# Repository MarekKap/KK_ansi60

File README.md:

# KK_ansi60
60% mechanical keyboard

KK_ansi60 keyboard is inspired by [GH60 open source keyboard](https://github.com/komar007/gh60).
Case and mounting plate are made from one piece of aluminium alloy. This feature allows very
solid and compact design. On the other hand only ane switch layout is supported.
Keyboard support TMK firmware, so everything is open source and customizable. On default there
are two base layers. Active layer is indicated with LED under FN1 or FN2 key.

## Build instructions
1. Solder all SMDs parts on PCB.
2. Temporary solder USB cable on connector `J1`.
3. Load firmware.
   1. Plug USB cable into computer.
   2. Run command `dmesg`, you should see `Product: ATm32U4DFU` in output list. If not,
      double check your soldering and check if you have ATMEGA32u4 with DFU bootloader.
   3. Clone repo `git clone "https://github.com/MarekKap/KK_ansi60"`.
   4. Go to firmware directory `cd KK_ansi60/Firmware/`.
   5. Compile program `make`.
   6. Load firmware into keyboard `sudo make dfu`.
   7. Unplug USB cable from computer.
4. Desolder USB cable.
5. Install keycaps stabilizers on top plate.
6. Install some switchies on on top plate. Start with edges and long keys.
7. Flip the top plate and put PCB on installed switches.
8. Cut switch legs. Keep in mind, there is only 2mm space between PCB and bottom plate.
9. Solder switches on PCB.
10. Install, cut and solder rest of the switches.
11. Install, cut and solder `LED1` and `LED2`.
12. Remove insulation from USB cable. Use heat shring tube or your nylon cable sleeve will
    start stripping over time.
13. Use cable tie to hold USB cable in place.
14. Solder free USB wires to connector `J1`. Keep `D+` and `D-` wires twisted as long as
    possible.
15. Hold down USB wires using kapton tape on PCB.
16. Install CNC legs with screws on bottom plate and put self adhesive pads in place.
17. Stick a insulation sticker on bottom plate (PCB side).
18. Screw bootom and top piece together with M2.5 screws.
19. Plug USB cable into computer and enjoy your keyboard. :-)

## Where to buy
| Item                        | Seller                       | Price [EUR] | Note                |
| --------------------------- | ---------------------------- | ----------- | ------------------- |
| Resistor 22R (R1, R2)       | [Farnell][1]                 |        0.09 | for 10 pcs          |
| Resistor 10K (R3, R4)       | [Farnell][2]                 |        0.09 | for 10 pcs          |
| Resistor 82R (R5, R6)       | [Farnell][3]                 |        0.13 | for 10 pcs          |
| Capacitor 10uF (C1)         | [Farnell][4]                 |        0.80 | for 5 pcs           |
| Capacitor 0.1uF (C2-C6, C8) | [Farnell][5]                 |        0.52 | for 10 pcs          |
| Capacitor 1uF (C7)          | [Farnell][6]                 |        1.33 | for 5 pcs           |
| Capacitor 22pF (C9, C10)    | [Farnell][7]                 |        1.23 | for 10 pcs          |
| White LED (LED1, LED2)      | [Farnell][8]                 |        2.54 | for 5 pcs           |
| Quartz 16MHz (Y1)           | [Farnell][9] or [Farnell][18]|        0.84 |                     |
| ATMEGA32u4 (U1)             | [Farnell][10]                |        3.71 |                     |
| Diode TS148 (D1-D61)        | [Farnell][11]                |        5.23 |                     |
| Switch (S1-S61)             | [AliExpress][12]             |       18.04 | 3 pin 65 pcs        |
| PCB                         | KK-electronic                |       25.00 | work in progress    |
| Stabilizers set             | [AliExpress][13]             |        7.20 | 6.25u plate mounted |
| USB cable                   | Any local store              |        3.00 |                     |
| Top Plate                   | KK-electronic                |      120.00 | work in progress    |
| Bottom Plate                | KK-electronic                |       40.00 | work in progress    |
| CNC Legs                    | [AliExpress][15]             |        3.00 | silver              |
| Self adhesive pads          | [AliExpress][16]             |       11.00 | for 500 pcs         |
| Insulation sticker          | KK-electronic                |       10.00 | work in progress    |
| Keycap set                  | [AliExpress][17]             |       21.00 |                     |

> If you are intrested in KK-electronic parts, please email at <kaplan.marek@gmail.com>.
> Price is approx. and can by significantly lower on group buy.

[1]: https://sk.farnell.com/multicomp/mcwr08x22r0ftl/res-22r-1-0-125w-0805-thick-film/dp/2447609
[2]: https://sk.farnell.com/multicomp/mcwr08x1002ftl/res-10k-1-0-125w-0805-thick-film/dp/2447553
[3]: https://sk.farnell.com/multicomp/mcmr08x820-jtl/res-82r-5-0-125w-0805-ceramic/dp/2073848
[4]: https://sk.farnell.com/kemet/c0805c106k8pactu/cap-10-f-10v-10-x5r-0805/dp/1463362 
[5]: https://sk.farnell.com/multicomp/mc0805b104m500ct/cap-0-1-f-50v-20-x7r-0805/dp/2627477
[6]: https://sk.farnell.com/multicomp/mc0805f105z500ct/cap-1-f-50v-y5v-0805/dp/1759432
[7]: https://sk.farnell.com/multicomp/mca0805c220jct/cap-22pf-100v-5-c0g-np0-0805/dp/9406247
[8]: https://sk.farnell.com/multicomp/mcl034swc-wh1/led-3mm-36-pure-white/dp/1581176
[9]: https://sk.farnell.com/qantek-technology-corporation/qc3216-0000f12b12m/crystal-16mhz-12pf-3-2mm-x-2-5mm/dp/2508646
[10]: https://sk.farnell.com/microchip/atmega32u4-au/mcu-8bit-megaavr-16mhz-tqfp-44/dp/1748525
[11]: https://sk.farnell.com/taiwan-semiconductor/ts4148-ryg/diode-small-signal-75v-0-15a-0805/dp/2708389
[12]: https://www.aliexpress.com/item/32797603005.html
[13]: https://www.aliexpress.com/item/32800781632.html
[15]: https://www.aliexpress.com/item/4000786300405.html
[16]: https://www.aliexpress.com/item/32242384655.html
[17]: https://www.aliexpress.com/item/32839583006.html
[18]: https://sk.farnell.com/multicomp/mcsjk-7u-16-00-12-30-80-b-30/crystal-16mhz-12pf-3-2mm-x-2-5mm/dp/2853937

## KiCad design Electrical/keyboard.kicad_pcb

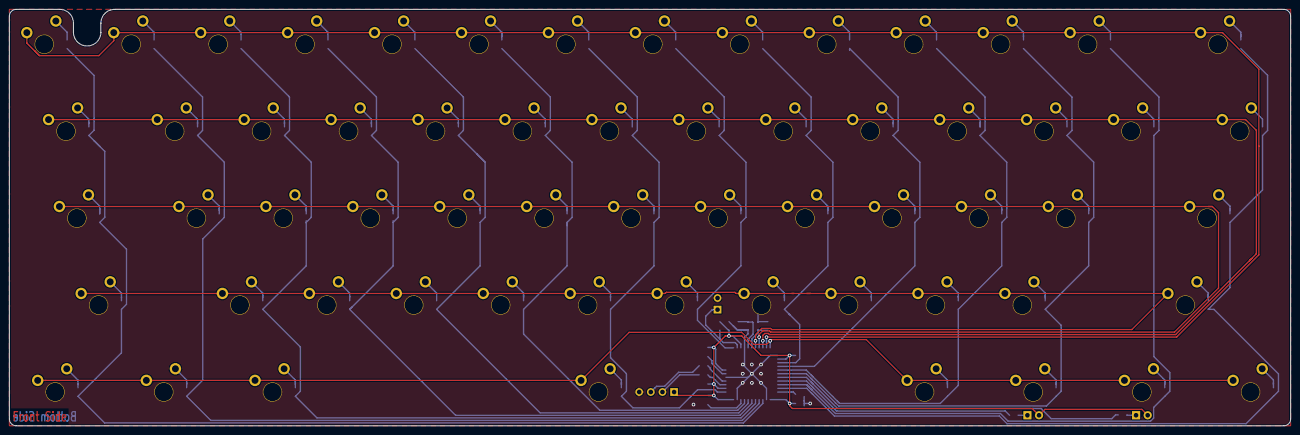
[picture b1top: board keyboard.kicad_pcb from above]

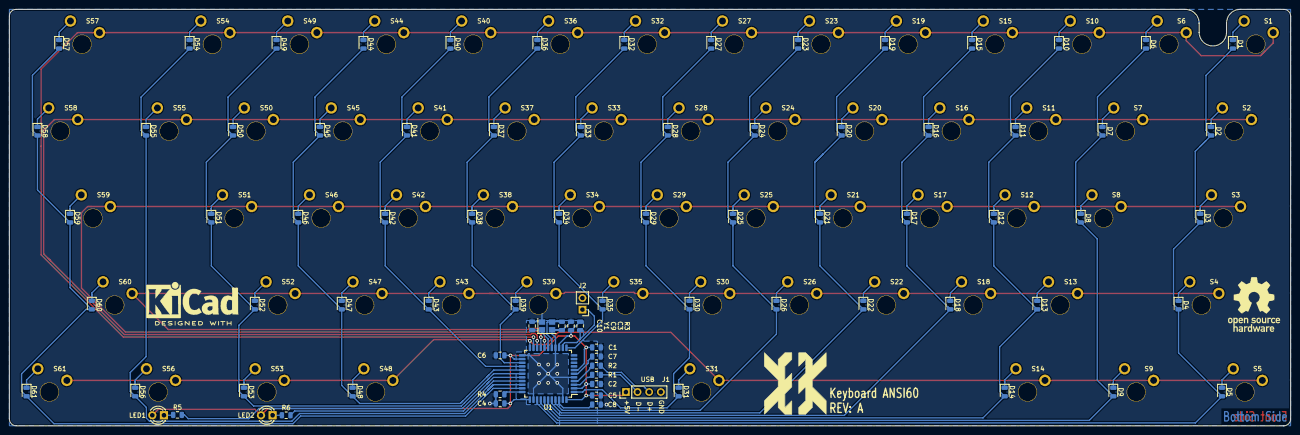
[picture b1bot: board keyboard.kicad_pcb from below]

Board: 2 copper layers, 280.0 x 91.0 mm, 144 parts (81 on the bottom side), 96 nets.

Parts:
C1: 10uF; C_0805_2012Metric
C2, C3, C4, C5, C6, C8: 0.1uF; C_0805_2012Metric
C7: 1uF; C_0805_2012Metric
C9, C10: 22pF; C_0805_2012Metric
D1, D2, D3, D4, D5, D6, D7, D8, D9, D10, D11, D12, D13, D14, D15, D16, D17, D18, D19, D20, D21, D22, D23, D24, D25, D26, D27, D28, D29, D30, D31, D32, D33, D34, D35, D36, D37, D38, D39, D40, D41, D42, D43, D44, D45, D46, D47, D48, D49, D50, D51, D52, D53, D54, D55, D56, D57, D58, D59, D60, D61: TS4148; D_0805_2012Metric
J1: USB; PinHeader_1x04_P2.54mm_Vertical
J2: Conn_01x02; PinHeader_1x02_P2.54mm_Vertical
LED1, LED2: White; LED_D3.0mm_Clear
R1, R2: 22; R_0805_2012Metric
R3, R4: 10k; R_0805_2012Metric
R5, R6: 82; R_0805_2012Metric
S1, S2, S3, S4, S5, S6, S7, S8, S9, S10, S11, S12, S13, S14, S15, S16, S17, S18, S19, S20, S21, S22, S23, S24, S25, S26, S27, S28, S29, S30, S31, S32, S33, S34, S35, S36, S37, S38, S39, S40, S41, S42, S43, S44, S45, S46, S47, S48, S49, S50, S51, S52, S53, S54, S55, S56, S57, S58, S59, S60, S61: MX1A; MX1A-plate
U1: ATMEGA32U4; LQFP-44_10x10mm_P0.8mm
Y1: 16MHz; Crystal_SMD_3225-4Pin_3.2x2.5mm

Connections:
+5V: C1.1, C2.1, C3.1, C4.1, C5.1, C6.1, J1.1, LED1.2, LED2.2, R3.2, U1.2, U1.7, U1.14, U1.24, U1.34, U1.44
/D+: J1.3, R2.1
/D-: J1.2, R1.2
/Matrix/col1: D1.2, D2.2, D3.2, D4.2, D5.2, U1.36
/Matrix/col2: D6.2, D7.2, D8.2, D9.2, U1.37
/Matrix/col3: D10.2, D11.2, D12.2, D13.2, D14.2, U1.38
/Matrix/col4: D15.2, D16.2, D17.2, D18.2, U1.39
/Matrix/col5: D19.2, D20.2, D21.2, D22.2, U1.40
/Matrix/col6: D23.2, D24.2, D25.2, D26.2, U1.41
/Matrix/col7: D27.2, D28.2, D29.2, D30.2, D31.2, U1.1
/Matrix/col8: D32.2, D33.2, D34.2, D35.2, U1.12
/Matrix/col9: D36.2, D37.2, D38.2, D39.2, U1.25
/Matrix/col10: D40.2, D41.2, D42.2, D43.2, U1.26
/Matrix/col11: D44.2, D45.2, D46.2, D47.2, D48.2, U1.27
/Matrix/col12: D49.2, D50.2, D51.2, D52.2, D53.2, U1.28
/Matrix/col13: D54.2, D55.2, D56.2, U1.31
/Matrix/col14: D57.2, D58.2, D59.2, D60.2, D61.2, U1.32
/Matrix/row1: S1.1, S6.1, S10.1, S15.1, S19.1, S23.1, S27.1, S32.1, S36.1, S40.1, S44.1, S49.1, S54.1, S57.1, U1.21
/Matrix/row2: S2.1, S7.1, S11.1, S16.1, S20.1, S24.1, S28.1, S33.1, S37.1, S41.1, S45.1, S50.1, S55.1, S58.1, U1.20
/Matrix/row3: S3.1, S8.1, S12.1, S17.1, S21.1, S25.1, S29.1, S34.1, S38.1, S42.1, S46.1, S51.1, S59.1, U1.19
/Matrix/row4: S4.1, S13.1, S18.1, S22.1, S26.1, S30.1, S35.1, S39.1, S43.1, S47.1, S52.1, S60.1, U1.18
/Matrix/row5: S5.1, S9.1, S14.1, S31.1, S48.1, S53.1, S56.1, S61.1, U1.22
GND: C1.2, C2.2, C3.2, C4.2, C5.2, C6.2, C7.2, C8.2, C9.1, C10.1, J1.4, J2.2, R4.2, U1.5, U1.15, U1.23, U1.35, U1.43, Y1.2, Y1.4
unnamed: C7.1, U1.6
unnamed: C8.1, U1.42
unnamed: C9.2, U1.16, Y1.3
unnamed: C10.2, U1.17, Y1.1
unnamed: D1.1, S1.2
unnamed: D2.1, S2.2
unnamed: D3.1, S3.2
unnamed: D4.1, S4.2
unnamed: D5.1, S5.2
unnamed: D6.1, S6.2
unnamed: D7.1, S7.2
unnamed: D8.1, S8.2
unnamed: D9.1, S9.2
unnamed: D10.1, S10.2
unnamed: D11.1, S11.2
unnamed: D12.1, S12.2
unnamed: D13.1, S13.2
unnamed: D14.1, S14.2
unnamed: D15.1, S15.2
unnamed: D16.1, S16.2
unnamed: D17.1, S17.2
unnamed: D18.1, S18.2
unnamed: D19.1, S19.2
unnamed: D20.1, S20.2
unnamed: D21.1, S21.2
unnamed: D22.1, S22.2
unnamed: D23.1, S23.2
unnamed: D24.1, S24.2
unnamed: D25.1, S25.2
unnamed: D26.1, S26.2
unnamed: D27.1, S27.2
unnamed: D28.1, S28.2
unnamed: D29.1, S29.2
unnamed: D30.1, S30.2
unnamed: D31.1, S31.2
unnamed: D32.1, S32.2
unnamed: D33.1, S33.2
unnamed: D34.1, S34.2
unnamed: D35.1, S35.2
unnamed: D36.1, S36.2
unnamed: D37.1, S37.2
unnamed: D38.1, S38.2
unnamed: D39.1, S39.2
unnamed: D40.1, S40.2
unnamed: D41.1, S41.2
unnamed: D42.1, S42.2
unnamed: D43.1, S43.2
unnamed: D44.1, S44.2
unnamed: D45.1, S45.2
unnamed: D46.1, S46.2
unnamed: D47.1, S47.2
unnamed: D48.1, S48.2
unnamed: D49.1, S49.2
unnamed: D50.1, S50.2
unnamed: D51.1, S51.2
unnamed: D52.1, S52.2
unnamed: D53.1, S53.2
unnamed: D54.1, S54.2
unnamed: D55.1, S55.2
unnamed: D56.1, S56.2
unnamed: D57.1, S57.2
unnamed: D58.1, S58.2
unnamed: D59.1, S59.2
unnamed: D60.1, S60.2
unnamed: D61.1, S61.2
unnamed: J2.1, R3.1, U1.13
unnamed: LED1.1, R5.1
unnamed: LED2.1, R6.1
unnamed: R1.1, U1.3
unnamed: R2.2, U1.4
unnamed: R4.1, U1.33
unnamed: R5.2, U1.29
unnamed: R6.2, U1.30

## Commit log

2020-02-27 new file: Electrical/doc/1n4148w.pdf new file: Electrical/doc/MX Series.pdf new file: Electrical/doc/QC32 SMD crystal.pdf new file: Electrical/doc/RoundLED.pdf new file: Electrical/doc/TS4148.pdf new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
2020-02-27 deleted: Other/Electrical/BOM.ods deleted: Other/Electrical/doc/1n4148w.pdf deleted: Other/Electrical/doc/MX Series.pdf deleted: Other/Electrical/doc/QC32 SMD crystal.pdf deleted: Other/Electrical/do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
2020-02-27 renamed: export/fabrication/README.txt -> fabrication/README.txt renamed: export/fabrication/keyboard-B_Cu.gbr -> fabrication/keyboard-B_Cu.gbr renamed: export/fabrication/keyboard-B_Mask.gbr -> fabr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
2020-04-12 add firmware
2020-04-12 led function update
2020-04-27 add build instructions
2020-04-27 title image fix
2020-04-27 title image fix2
2020-05-08 where to buy section in README
2020-05-15 KK_ANSI60_bottom.dxf update
2020-06-25 modified: KK_ANSI60_top.dxf new file: KK_ANSI60_top_drawing.dxf
2021-02-20 modified: README.md add Quartz 16MHz alternative
